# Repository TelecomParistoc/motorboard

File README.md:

# motorboardv2
carte permettant de piloter les moteurs et de suivre la position actuelle

## Objectifs
La carte devra répondre aux objectifs suivant :

* permettre l'asservissement en position des moteurs, contrôlé par le Raspberry Pi
* controler l'IMU et faire la fusion avec les roues codeuses pour contre-balancer le lag du BNO055
* faire la fusion de la radio, de l'IMU et des roues codeuses pour obtenir la position absolue

## Vue Système

En plus des liens vers les roues codeuses et le pont-en-H, il est nécessaire de fournir 3 ports :
* Un port esclave sur le bus I2C principal du robot, permettant la communication avec le Raspberry Pi
* Un port maitre SPI pour une liaison direct rapide à faible latence avec la carte radio
* un port I2C maitre pour contrôler l'IMU

La carte n'est pas responsable de l'alimentation de puissance du pont-en-H et les moteur mais fourni l'alimentation logique.

## Contraintes

#### MC1 Configuration des connecteurs
Afin d'assurer la compatibilité avec les éléments existants, la configuration des connecteurs est spécifiée dans [motorboard connectors.pdf](https://github.com/TelecomParistoc/motorboardv2/blob/master/specs/motorboard%20connectors.pdf)

#### MC2 Emplacement des trous de fixation
La carte sera montée au dessus de la carte pont-en-H existante, les trous de fixation devront donc être alignés pour permettre le passage des vis.

## Solution proposée

### Contrôleur

Afin de rendre le portage du code existant facile et d'accélerer le développement, la série STM32F302x8/6 a été sélectionnée. 
Le **STM32F302C8** a été retenu.

| MCU | STM32F302C8T6 |
| ----- | ------------- |
| Coeur | Cortex M4F |
| Horloge | Interne 64MHz |
| Flash | 64Ko |
| RAM | 16Ko |
| SPI | 2 |
| I2C | 3 |
| boitier | LQFP48 |

### Alimentation

| Sous-système | Consommation max. |
| --- | -------------- |
| LED (5V) | 1 mA |
| Roues codeuses (5V) | 120 mA |
| **Total 5V** | **121 mA** |
| Logique pont-en-H (3.3V) | 8 mA |
| IMU (3.3V) | 12.5 mA |
| Contrôleur (3.3V) | 42 mA |
| LEDs (3.3V) | 3.5 mA |
| **Total 3.3V** | **66 mA** |

La consommation maximum sur le 3.3V est jugée raisonnable, il n'est pas nécessaire d'ajouter un régulateur local.

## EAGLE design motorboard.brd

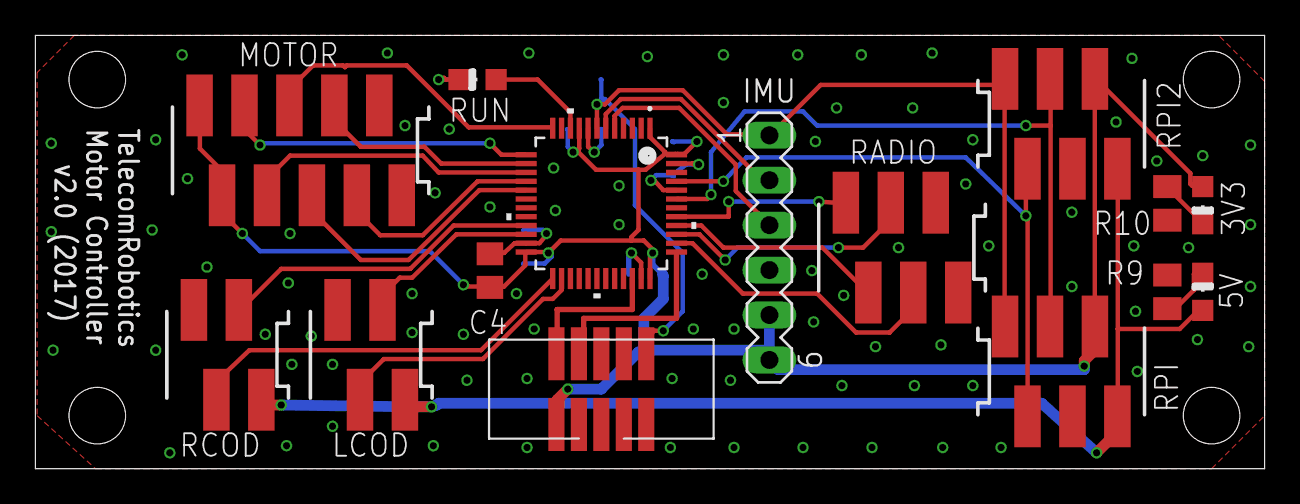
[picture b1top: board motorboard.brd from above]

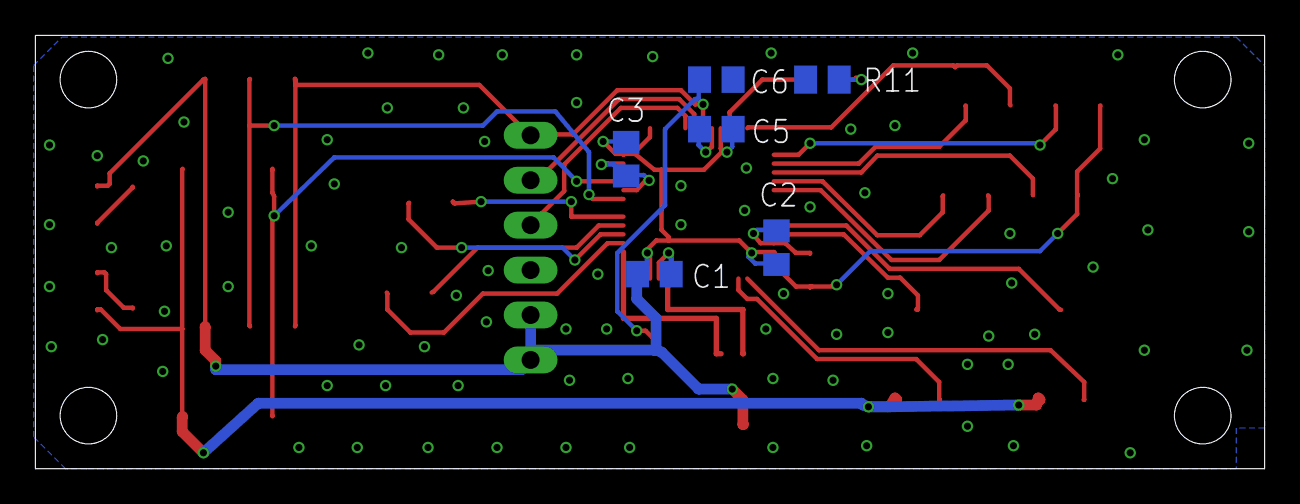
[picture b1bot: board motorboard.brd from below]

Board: 2 copper layers, 69.5 x 24.5 mm, 21 parts (6 on the bottom side), 28 nets.

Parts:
3V3, 5V: CHIPLED_0805
C1, C2, C3, C6: 100n; C0805
C4: 10uF; C0805
C5: 100nF; C0805
IMU: MA06-1
LCOD: SMDTOP4
MOTOR: SMDTOP10
R9: 4.7k; M0805
R10: 2.2k; M0805
R11: 1k; M0805
RADIO: SMDTOP6
RCOD: SMDTOP4
RPI, RPI2: SMDTOP6
RUN: CHIPLED_0805
U1: STM32F302_303C2; LQFP48-7X7MM
U$1: SWD/JTAG-_PINS; SAMTEC_SHF-105-01-L-D-SM

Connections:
GND: C1.2, C2.2, C3.2, C4.2, C5.2, C6.2, IMU.4, LCOD.1, MOTOR.9, MOTOR.10, R9.2, R10.2, R11.2, RADIO.5, RADIO.6, RCOD.1, RPI.3, RPI2.3, U1.8, U1.23, U1.35, U1.44, U1.47, U$1.P$3, U$1.P$5, U$1.P$9
IMU_SCL: IMU.2, U1.6
IMU_SDA: IMU.3, U1.5
LCODA: LCOD.3, U1.22
LCODB: LCOD.2, U1.26
LMOTA: MOTOR.8, U1.16
LMOTB: MOTOR.4, U1.15
LMOTPWM: MOTOR.6, U1.17
unnamed: RUN.A, U1.10
unnamed: R11.1, RUN.C
unnamed: 5V.C, R9.1
unnamed: 3V3.C, R10.1
N_RESET: C6.1, IMU.1, RPI.6, RPI2.6, U1.7, U$1.P$10
RAD_MISO: RADIO.2, U1.40
RAD_MOSI: RADIO.1, U1.41
RAD_N_CS: RADIO.4, U1.38
RAD_SCK: RADIO.3, U1.39
RCODA: RCOD.3, U1.21
RCODB: RCOD.2, U1.25
RMOTA: MOTOR.3, U1.13
RMOTB: MOTOR.7, U1.14
RMOTPWM: MOTOR.5, U1.12
RPI_SCL: RPI.5, RPI2.5, U1.45
RPI_SDA: RPI.4, RPI2.4, U1.43
SWD_CLK: U1.37, U$1.P$4
SWD_DIO: U1.34, U$1.P$2
VCC: 3V3.A, C1.1, C2.1, C3.1, C4.1, C5.1, IMU.5, IMU.6, MOTOR.1, MOTOR.2, RPI.2, RPI2.2, U1.1, U1.9, U1.24, U1.36, U1.48, U$1.P$1
VDD: 5V.A, LCOD.4, RCOD.4, RPI.1, RPI2.1

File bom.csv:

Qty;Qty to buy;Value;Device;Package;Parts;Description;Distributor
3;0;;LEDCHIPLED_0805;CHIPLED_0805;3V3, 5V, RUN;LED;
1;0;;MA06-1;MA06-1;IMU;PIN HEADER;
1;0;;SMDTOP-10;SMDTOP10;MOTOR;AMP connector;
2;0;;SMDTOP-4;SMDTOP4;LCOD, RCOD;AMP connector;
4;0;100nF;C-EUC0805;C0805;C1, C2, C3, C6;CAPACITOR;
1;0;1k;R-US_M0805;M0805;R11;RESISTOR;
1;0;2.2k;R-US_M0805;M0805;R10;RESISTOR;
1;0;4.7k;R-US_M0805;M0805;R9;RESISTOR;
1;1;4.7uF;C-EUC0805;C0805;C5;CAPACITOR;FARNELL 1759420
1;1;10uF;C-EUC0805;C0805;C4;CAPACITOR;FARNELL 2320856
1;1;STM32F302_303C2;STM32F302_303C2;LQFP48-7X7MM;U1;;MOUSER 511-STM32F302C8T6
1;1;SWD/JTAG-_PINS;SWD/JTAG-_PINS;SAMTEC_SHF-105-01-L-D-SM;U$1;;FARNELL 1885915
3;3;;SMDTOP-6;SMDTOP6;RADIO, RPI, RPI2;AMP connector;FARNELL 2473376, FARNELL 2473358

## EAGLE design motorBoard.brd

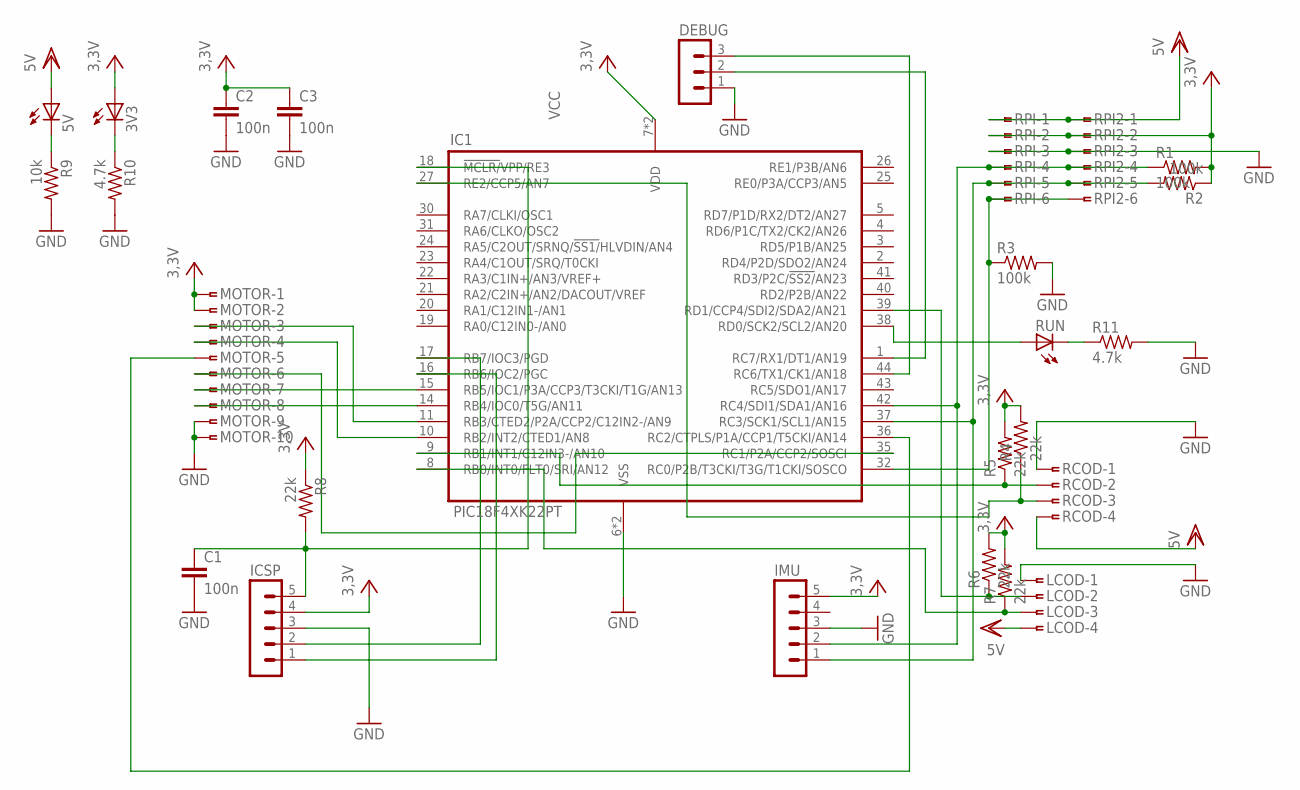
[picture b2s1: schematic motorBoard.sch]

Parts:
3V3, 5V: LEDCHIPLED_0805; CHIPLED_0805
C1, C2, C3: 100n; C0805
DEBUG: MA03-1
IC1: PIC18F4XK22PT; TQFP44
ICSP: MA05-1
IMU: MA05-1
LCOD: SMDTOP-4; SMDTOP4
MOTOR: SMDTOP-10; SMDTOP10
R1, R2, R3: 100k; R0805
R4, R5, R6, R7: 22k; R0805
R8: 22k; M0805
R9: 10k; M0805
R10, R11: 4.7k; M0805
RCOD: SMDTOP-4; SMDTOP4
RPI, RPI2: SMDTOP-6; SMDTOP6
RUN: LEDCHIPLED_0805; CHIPLED_0805

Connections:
GND: C1.2, C2.2, C3.2, DEBUG.1, IC1.6 (VSS), IC1.29 (VSS), ICSP.3, IMU.3, LCOD.1, MOTOR.9, MOTOR.10, R3.2, R9.2, R10.2, R11.2, RCOD.1, RPI.3, RPI2.3
unnamed: IC1.27 (RE2/CCP5/AN7), R4.1, RCOD.3
unnamed: IC1.11 (RB3/CTED2/P2A/CCP2/C12IN2-/AN9), MOTOR.3
unnamed: IC1.10 (RB2/INT2/CTED1/AN8), MOTOR.4
unnamed: IC1.35 (RC1/P2A/CCP2/SOSCI), MOTOR.6
unnamed: IC1.16 (RB6/IOC2/PGC), ICSP.1
unnamed: IC1.14 (RB4/IOC0/T5G/AN11), MOTOR.8
unnamed: IC1.8 (RB0/INT0/FLT0/SRI/AN12), LCOD.3, R7.1
unnamed: IC1.15 (RB5/IOC1/P3A/CCP3/T3CKI/T1G/AN13), MOTOR.7
unnamed: R11.1, RUN.C
unnamed: 5V.C, R9.1
unnamed: IC1.39 (RD1/CCP4/SDI2/SDA2/AN21), LCOD.2, R6.1
unnamed: DEBUG.2, IC1.1 (RC7/RX1/DT1/AN19)
unnamed: IC1.9 (RB1/INT1/C12IN3-/AN10), R5.1, RCOD.2
unnamed: 3V3.C, R10.1
unnamed: IC1.38 (RD0/SCK2/SCL2/AN20), RUN.A
unnamed: DEBUG.3, IC1.44 (RC6/TX1/CK1/AN18)
unnamed: IC1.17 (RB7/IOC3/PGD), ICSP.2
unnamed: C1.1, IC1.18 (!MCLR/!VPP/RE3), ICSP.5, R8.2
unnamed: IC1.42 (RC4/SDI1/SDA1/AN16), IMU.2, R1.1, RPI.4, RPI2.4
unnamed: IC1.37 (RC3/SCK1/SCL1/AN15), IMU.1, R2.2, RPI.5, RPI2.5
unnamed: IC1.32 (RC0/P2B/T3CKI/T3G/T1CKI/SOSCO), R3.1, RPI.6, RPI2.6
unnamed: IC1.36 (RC2/CTPLS/P1A/CCP1/T5CKI/AN14), MOTOR.5
VCC: 3V3.A, C2.1, C3.1, IC1.7 (VDD), IC1.28 (VDD), ICSP.4, IMU.5, MOTOR.1, MOTOR.2, R1.2, R2.1, R4.2, R5.2, R6.2, R7.2, R8.1, RPI.2, RPI2.2
VDD: 5V.A, LCOD.4, RCOD.4, RPI.1, RPI2.1

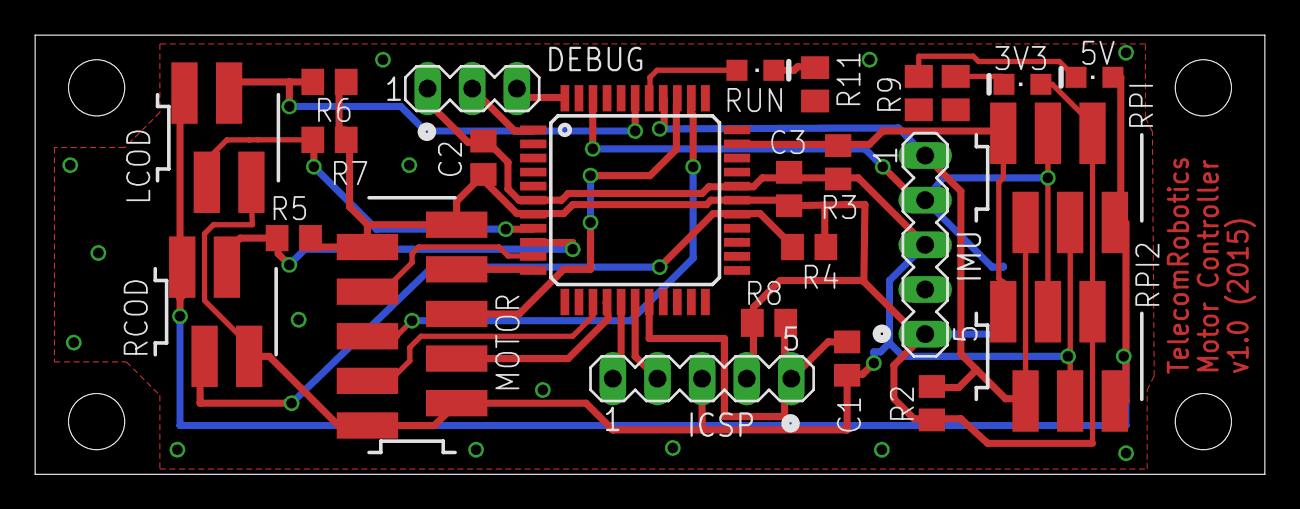
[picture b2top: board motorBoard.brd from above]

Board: 2 copper layers, 70.0 x 25.0 mm, 26 parts (1 on the bottom side), 25 nets.

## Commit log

2015-12-19 WIP updated schematic and created a new smaller board
2015-12-19 include components libraries
2015-12-19 fixed schematic and replaced some connectors with micromatch
2015-12-25 board almost finished
2015-12-25 connected polygones to GND and added some vias
2015-12-25 modified text
2015-12-29 added power and status LEDs, fixed silkscreen
2015-12-29 added some more vias
2015-12-31 added datasheets of used parts
2017-03-11 added libraries and datasheets
2017-03-12 schematics and board v1, added connectors spec
2017-03-12 added pdf of board and schematics
2017-03-12 added stmcube project file
2017-03-12 hidden retrict areas
2017-03-12 ajout contraintes et solution
2017-03-12 fixed problems shown by Eurocircuit pcbview
2017-03-12 fixed capacitors values
2017-03-12 added BOM
2017-03-12 updated H-bridge link in architecture
2017-03-19 added distributor refs to bom

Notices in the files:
parts and their libraries:
COPYRIGHT: Copyright C 2016 Accelerated Designs. All rights reserved
